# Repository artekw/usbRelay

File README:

simple "relay" controled via USB

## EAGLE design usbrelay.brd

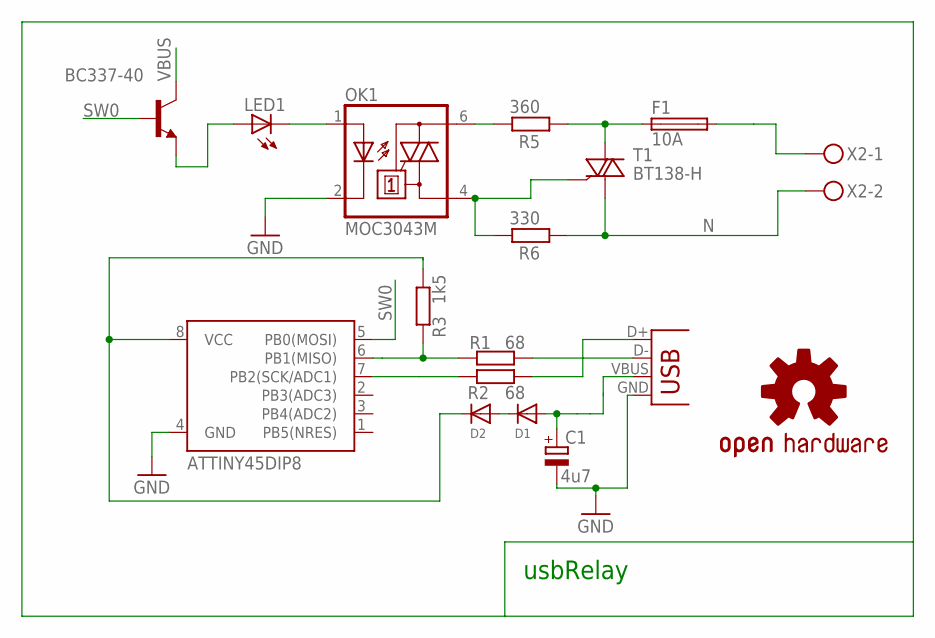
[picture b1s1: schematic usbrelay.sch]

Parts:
C1: 4u7; E5-4
D1, D2: DIODEDO-1N4148; DO-1N4148
F1: 10A; FUSE_HOLDER_5X20MM
LED1: LED3MM
OK1: MOC3043M; DIL06
Q1: BC337-40; TO92
R1, R2: 68; 0204/5
R3: 1k5; 0204/5
R5: 360; 0204/5
R6: 330; 0204/5
T1: BT138-H; TO220BH
U$1: ATTINY45DIP8; DIP08
U$2: OSHW-LOGOM; OSHW-LOGO-M
X1: USBPTH; USB-B-PTH
X2: MKDSN1,5/2-5,08

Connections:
GND: C1.-, U$1.4 (GND), X1.GND
N: R6.1, T1.T1 (A1), X2.2
unnamed: D1.C, D2.A
unnamed: R1.2, X1.D-
unnamed: R1.1, R3.1, U$1.6 (PB1(MISO))
unnamed: R2.2, X1.D+
unnamed: R2.1, U$1.7 (PB2(SCK/ADC1))
unnamed: LED1.A, Q1.1 (E)
unnamed: D2.C, R3.2, U$1.8 (VCC)
unnamed: LED1.K (C), OK1.1 (A)
unnamed: OK1.6 (A2), R5.2
unnamed: F1.1, R5.1, T1.T2 (A2)
unnamed: OK1.4 (A1), R6.2, T1.G
unnamed: F1.2, X2.1
SW0: U$1.5 (PB0(MOSI))
VBUS: C1.+, D1.A, Q1.3 (C), X1.VBUS

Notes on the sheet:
usbRelay

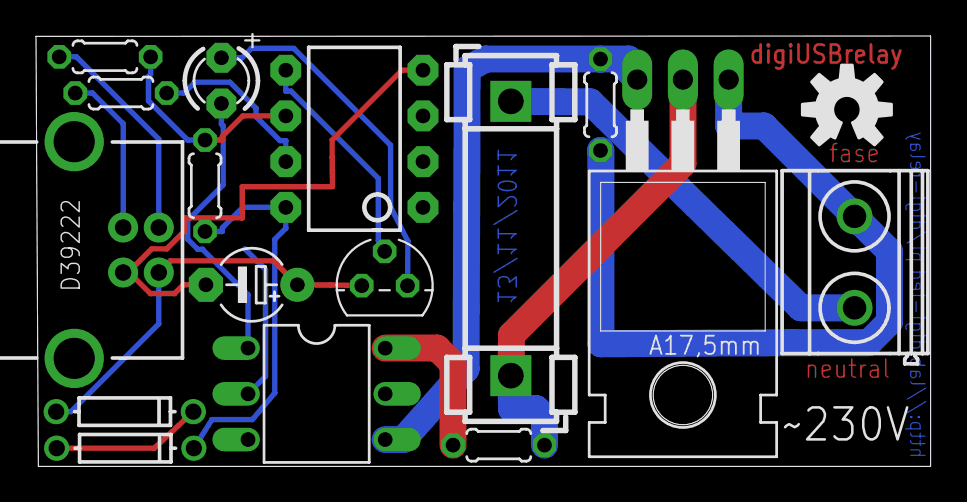
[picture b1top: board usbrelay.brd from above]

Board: 2 copper layers, 49.7 x 23.9 mm, 17 parts (0 on the bottom side), 15 nets.

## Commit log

2011-11-12 add README
2011-11-12 rename file
2011-12-17 latest work - fully working device
2011-12-17 README changes
2011-12-17 sheet and pcb
2011-12-20 clean up and add sources usbrelay for OpenWrt firmware
2011-12-23 upload final files of project, read README file for more information
2011-12-23 upload md5sum for binary files
2012-01-25 current work
2012-01-25 schematics
2012-01-25 pdf of schematics and pdf
2012-01-25 commandline
2012-01-28 clean up binaries
2012-01-28 fix deps
